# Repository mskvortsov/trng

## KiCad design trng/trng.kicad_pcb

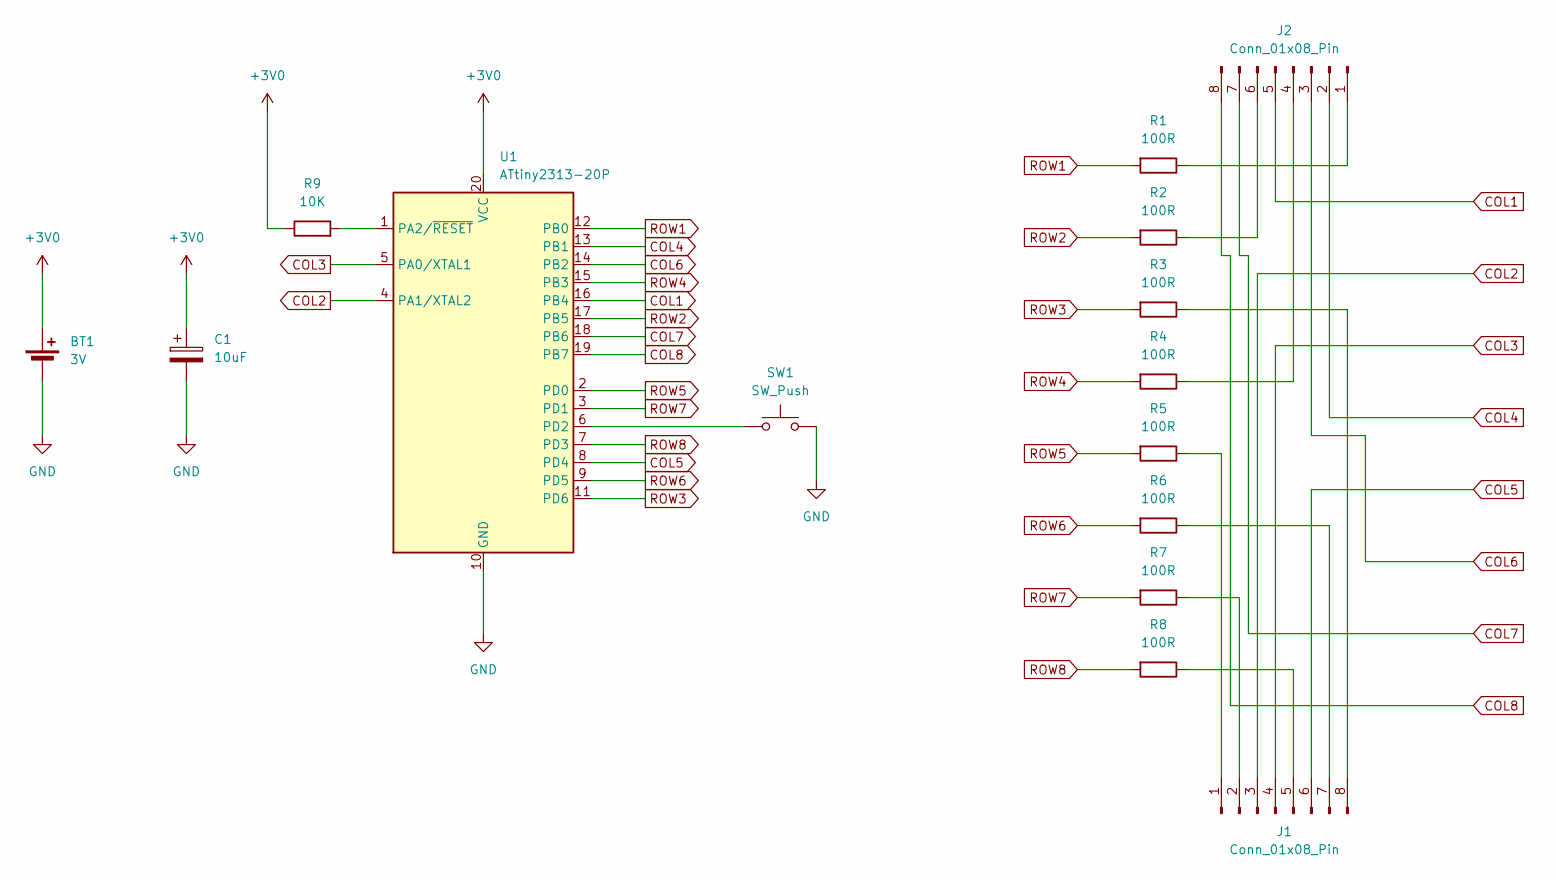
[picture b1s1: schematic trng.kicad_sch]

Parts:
BT1: 3V; BatteryHolder_Keystone_107_1x23mm
C1: 10uF; CP_Radial_D4.0mm_P1.50mm
J1, J2: Conn_01x08_Pin; PinSocket_1x08_P2.54mm_Vertical
R1, R2, R3, R4, R5, R6, R7, R8: 100R; R_Axial_DIN0204_L3.6mm_D1.6mm_P1.90mm_Vertical
R9: 10K; R_Axial_DIN0204_L3.6mm_D1.6mm_P1.90mm_Vertical
SW1: SW_Push; SW_PUSH-12mm
U1: ATtiny2313-20P; DIP-20_W7.62mm

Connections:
+3V0: BT1.1 (+), C1.1, R9.1, U1.20 (VCC)
COL1: J2.5, U1.16 (PB4)
COL2: J1.3, U1.4 (PA1/XTAL2)
COL3: J1.4, U1.5 (PA0/XTAL1)
COL4: J2.2, U1.13 (PB1)
COL5: J1.6, U1.8 (PD4)
COL6: J2.3, U1.14 (PB2)
COL7: J2.7, U1.18 (PB6)
COL8: J2.8, U1.19 (PB7)
GND: BT1.2 (-), C1.2, SW1.2, U1.10 (GND)
unnamed: J1.1, R5.1
unnamed: J1.2, R7.1
unnamed: J1.5, R8.1
unnamed: J1.7, R6.1
unnamed: J1.8, R3.1
unnamed: J2.1, R1.1
unnamed: J2.4, R4.1
unnamed: J2.6, R2.1
unnamed: R9.2, U1.1 (PA2/~RESET)
unnamed: SW1.1, U1.6 (PD2)
ROW1: R1.2, U1.12 (PB0)
ROW2: R2.2, U1.17 (PB5)
ROW3: R3.2, U1.11 (PD6)
ROW4: R4.2, U1.15 (PB3)
ROW5: R5.2, U1.2 (PD0)
ROW6: R6.2, U1.9 (PD5)
ROW7: R7.2, U1.3 (PD1)
ROW8: R8.2, U1.7 (PD3)

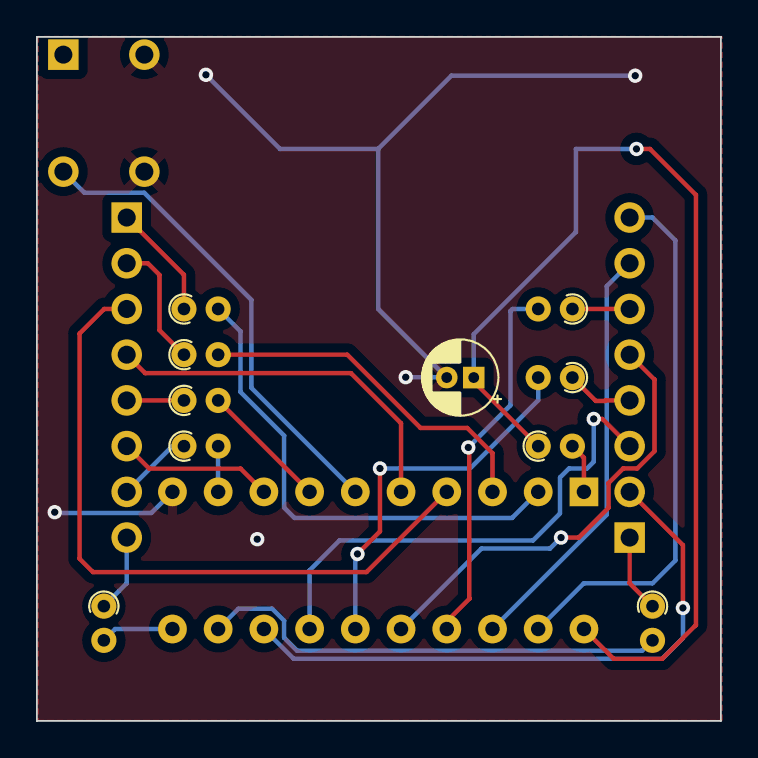
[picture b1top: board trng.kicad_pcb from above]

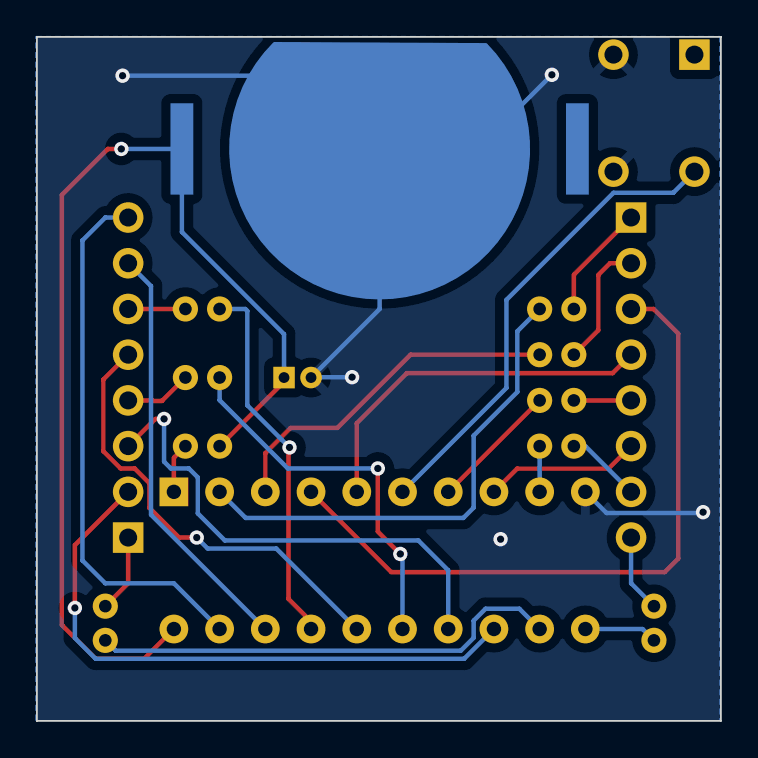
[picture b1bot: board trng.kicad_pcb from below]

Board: 2 copper layers, 38.0 x 38.0 mm, 15 parts (2 on the bottom side), 28 nets.

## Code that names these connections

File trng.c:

#ifndef F_CPU
#define F_CPU 1000000UL
#endif

#include <avr/interrupt.h>
#include <avr/io.h>
#include <avr/sleep.h>
#include <avr/wdt.h>
#include <util/delay.h>
#include <string.h>

static const int ROW_DELAY = 500;
static const int SHOW_CYCLES = 1000;
static const int NEXT_ALLOW_CYCLE = 100;

static uint8_t random_block[8] = { 0 };
static volatile uint8_t random_block_ready = 0;

static uint8_t stir(uint8_t r, uint8_t sample) {
  return ((r << 1) | (r >> 7)) ^ sample;
}

ISR(WDT_OVERFLOW_vect) {
  static uint8_t bits = 0;
  static uint8_t bits_ready = 0;
  uint8_t sample = TCNT1L;

  bits = stir(bits, sample);
  bits_ready += 1;

  if ((bits_ready & 7) == 0) {
    random_block[(bits_ready >> 3) - 1] = bits;
    if (bits_ready == 64) {
      bits_ready = 0;
      random_block_ready = 1;
      wdt_disable();
    }
  }
}

static void reset_row() {
  PORTB &= ~_BV(PB0);
  PORTB &= ~_BV(PB5);
  PORTD &= ~_BV(PD6);
  PORTB &= ~_BV(PB3);
  PORTD &= ~_BV(PD0);
  PORTD &= ~_BV(PD5);
  PORTD &= ~_BV(PD1);
  PORTD &= ~_BV(PD3);
}

static void reset_col() {
  PORTB |= _BV(PB4);
  PORTA |= _BV(PA1);
  PORTA |= _BV(PA0);
  PORTB |= _BV(PB1);
  PORTD |= _BV(PD4);
  PORTB |= _BV(PB2);
  PORTB |= _BV(PB6);
  PORTB |= _BV(PB7);
}

static void set_row(uint8_t r) {
  switch (r) {
    case 0: PORTB |= _BV(PB0); break;
    case 1: PORTB |= _BV(PB5); break;
    case 2: PORTD |= _BV(PD6); break;
    case 3: PORTB |= _BV(PB3); break;
    case 4: PORTD |= _BV(PD0); break;
    case 5: PORTD |= _BV(PD5); break;
    case 6: PORTD |= _BV(PD1); break;
    case 7: PORTD |= _BV(PD3); break;
  }
}

static void set_col(uint8_t c) {
  switch (c) {
    case 0: PORTB &= ~_BV(PB4); break;
    case 1: PORTA &= ~_BV(PA1); break;
    case 2: PORTA &= ~_BV(PA0); break;
    case 3: PORTB &= ~_BV(PB1); break;
    case 4: PORTD &= ~_BV(PD4); break;
    case 5: PORTB &= ~_BV(PB2); break;
    case 6: PORTB &= ~_BV(PB6); break;
    case 7: PORTB &= ~_BV(PB7); break;
  }
}

static void set_cols(uint8_t cols) {
  for (uint8_t i = 0; i < 8; ++i) {
    if (cols & 1) {
      set_col(i);
    }
    cols >>= 1;
  }
}

static void show_random_block() {
  // show the rows one by one
  for (uint8_t r = 0; r < 8; ++r) {
    set_row(r);
    set_cols(random_block[r]);
    _delay_us(ROW_DELAY);
    reset_row();
    reset_col();
  }
}

static volatile uint8_t int0_fired = 0;
ISR(INT0_vect) {
  // disable INT0 interrupt
  GIMSK &= ~_BV(INT0);
  int0_fired = 1;
}

static void wdt_enable_16ms_interrupt() {
  // enable WDT interrupt
  // set the shortest possible timeout of 16ms
  WDTCSR |= (1 << WDCE) | (1 << WDE);
  WDTCSR = 1 << WDIE;
}

static void collect_entropy() {
  // start collecting entropy
  wdt_enable_16ms_interrupt();

  // wait for a new random block and blink
  uint8_t n = 20;
  while (random_block_ready == 0) {
    set_row(7);
    set_col(0);
    _delay_ms(20);
    reset_row();
    reset_col();
    for (int i = 0; i < n; ++i) {
      _delay_ms(20);
    }
    if (n > 1) {
      n >>= 1;
    }
  }
  random_block_ready = 0;
}

static void setup() {
  // disable analog comparator
  ACSR |= 1 << ACD;
  // disable AIN0 and AIN1 digital input
  DIDR = (1 << AIN1D) | (1 << AIN0D);

  DDRA |= _BV(PA0) | _BV(PA1); // PA2 is RESET
  DDRB |= 0xff;
  DDRD |= 0x7b; // PD2 (INT0) is input, PD7 is unavailable
  PORTD |= _BV(PD2); // pull up the INT0 pin

  reset_row();
  reset_col();

  // enable Timer1 w/o prescaler
  TCCR1B = 1 << CS10;

  set_sleep_mode(SLEEP_MODE_PWR_DOWN);
  sleep_enable();

  sei();
}

int main() {
  setup();

  while (1) {
    // show the random block
    for (int counter = 0; counter < SHOW_CYCLES; ++counter) {
      show_random_block();
      // enable INT0 interrupt after a while
      if (counter == NEXT_ALLOW_CYCLE) {
        int0_fired = 0;
        GIMSK |= _BV(INT0);
      }
      if (int0_fired) {
        break;
      }
    }

    if (int0_fired) {
      int0_fired = 0;
      collect_entropy();
      continue; // show new block again
    }

    // enable INT0 interrupt
    GIMSK |= _BV(INT0);
    // enter power-down mode
    sleep_mode();

    // wake-up occurs here
    int0_fired = 0;
  }
}
